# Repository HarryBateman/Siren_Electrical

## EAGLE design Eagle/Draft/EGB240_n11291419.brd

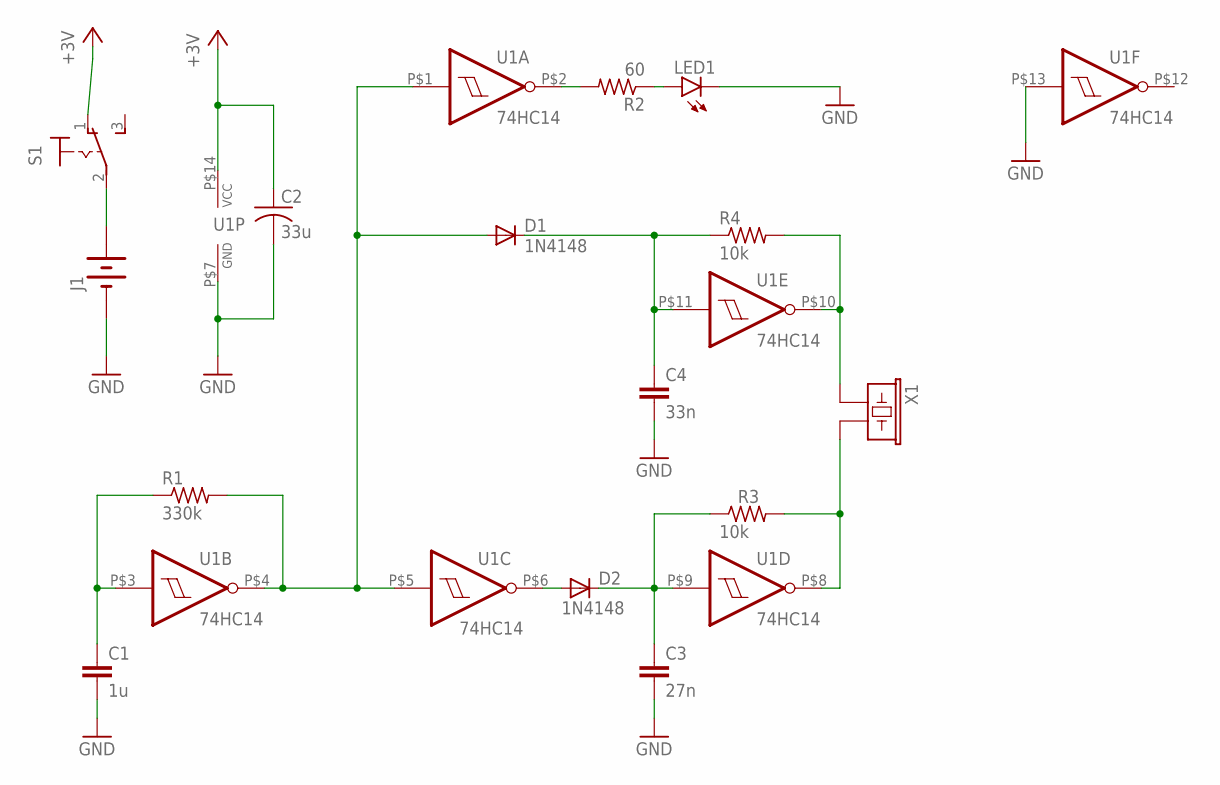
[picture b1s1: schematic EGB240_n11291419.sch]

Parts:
C1: 1u; CAP-DISC-P5.08
C2: 33u; CAP-RB-P2.0-D5.0
C3: 27n; CAP-MKT-7.5X3.2-P5.08
C4: 33n; CAP-MKT-7.5X3.2-P5.08
D1, D2: 1N4148; DO35-P7.62
J1: BATTERY-3VBATT; BATT-3V
LED1: LED5MM
R1: 330k; AXIAL-P2.54
R2: 60; AXIAL-P2.54
R3, R4: 10k; AXIAL-P2.54
S1: SWITCH-SPDT; SS-12
U1: 74HC14; DIP-14
X1: BUZZER-PIEZOPS1720P02; PS1720P02

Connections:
+3V: C2.P$1 (1), S1.1 (O), U1.P$14 (VCC)
GND: C1.P$2 (2), C2.P$2 (2), C3.P$2 (2), C4.P$2 (2), J1.P$2 (-), LED1.K (C), U1.P$7 (GND), U1.P$13 (I)
unnamed: J1.P$1 (+), S1.2
unnamed: C1.P$1 (1), R1.P$1 (1), U1.P$3 (I)
unnamed: D1.A, R1.P$2 (2), U1.P$1 (I), U1.P$4 (O), U1.P$5 (I)
unnamed: R4.P$2 (2), U1.P$10 (O), X1.P$1 (1)
unnamed: R3.P$2 (2), U1.P$8 (O), X1.P$2 (2)
unnamed: C4.P$1 (1), D1.K, R4.P$1 (1), U1.P$11 (I)
unnamed: C3.P$1 (1), D2.K, R3.P$1 (1), U1.P$9 (I)
unnamed: LED1.A, R2.P$1 (1)
unnamed: R2.P$2 (2), U1.P$2 (O)
unnamed: D2.A, U1.P$6 (O)

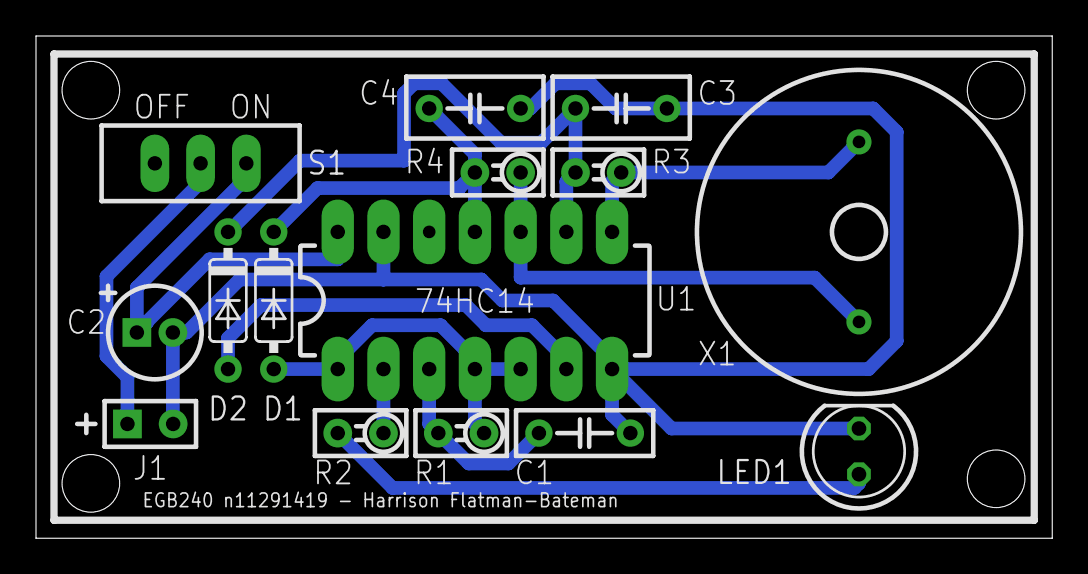
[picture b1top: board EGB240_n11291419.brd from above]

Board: 2 copper layers, 56.5 x 27.9 mm, 15 parts (0 on the bottom side), 12 nets.

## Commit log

2024-12-18 all data
